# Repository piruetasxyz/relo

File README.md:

# relo
módulo de señal de reloj

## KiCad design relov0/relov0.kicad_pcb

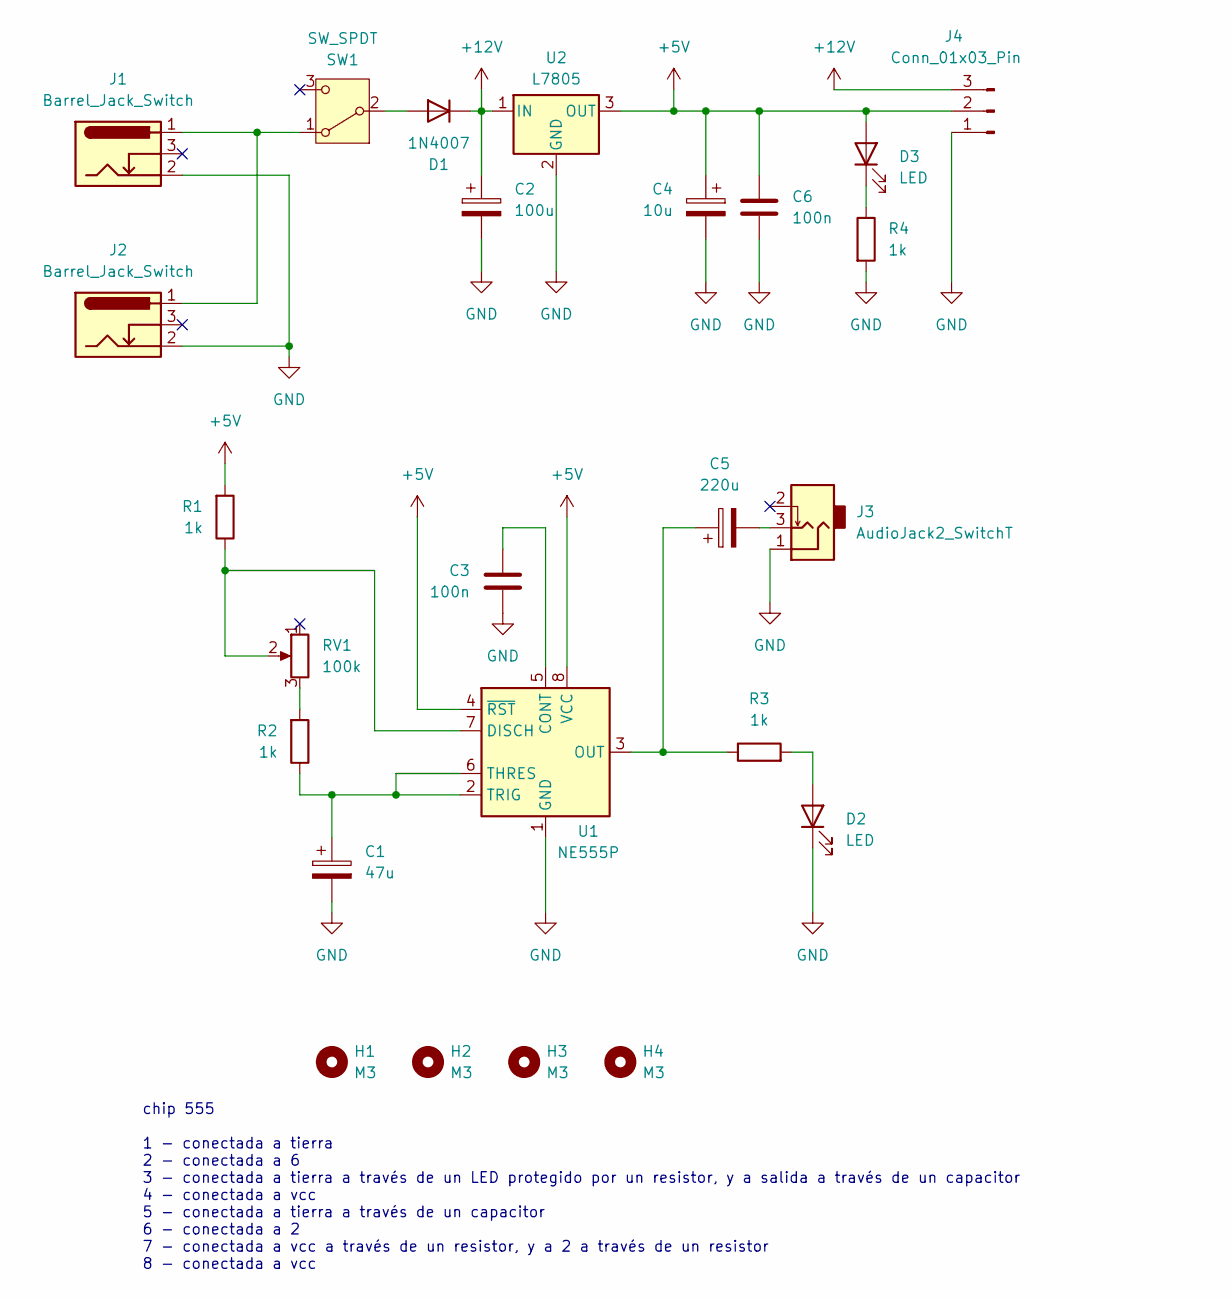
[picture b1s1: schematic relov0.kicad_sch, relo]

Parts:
C1: 47u; CP_Radial_D5.0mm_P2.00mm
C2: 100u; CP_Radial_D8.0mm_P3.80mm
C3, C6: 100n; C_Disc_D5.0mm_W2.5mm_P2.50mm
C4: 10u; CP_Radial_D4.0mm_P2.00mm
C5: 220u; CP_Radial_D5.0mm_P2.00mm
D1: 1N4007; D_DO-41_SOD81_P10.16mm_Horizontal
D2, D3: LED; LED_D5.0mm
H1, H2, H3, H4: M3; MountingHole_3.2mm_M3
J1, J2: Barrel_Jack_Switch; BarrelJack_Horizontal
J3: AudioJack2_SwitchT; PJ301M-12
J4: Conn_01x03_Pin; PinSocket_1x03_P2.54mm_Vertical
R1, R2, R3, R4: 1k; R_Axial_DIN0207_L6.3mm_D2.5mm_P10.16mm_Horizontal
RV1: 100k; Potentiometer_Alps_RK163_Single_Horizontal
SW1: SW_SPDT; spdt_ssd12d00g3
U1: NE555P; DIP-8_W7.62mm_Socket_LongPads
U2: L7805; TO-220-3_Horizontal_TabDown

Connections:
+5V: C4.1, C6.1, D3.2 (A), J4.2, R1.2, U1.4 (~RST), U1.8 (VCC), U2.3 (OUT)
+12V: C2.1, D1.1 (K), J4.3, U2.1 (IN)
GND: C1.2, C2.2, C3.1, C4.2, C6.2, D2.1 (K), J1.2, J2.2, J3.1, J4.1, R4.2, U1.1 (GND), U2.2 (GND)
unnamed: C5.2, J3.3
unnamed: D1.2 (A), SW1.2 (B)
unnamed: D2.2 (A), R3.2
unnamed: D3.1 (K), R4.1
unnamed: R2.2, RV1.3
unnamed: J1.1, J2.1, SW1.1 (A)
unnamed: C3.2, U1.5 (CONT)
unnamed: R1.1, RV1.2, U1.7 (DISCH)
unnamed: C5.1, R3.1, U1.3 (OUT)
unnamed: C1.1, R2.1, U1.2 (TRIG), U1.6 (THRES)

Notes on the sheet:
chip 555 1 - conectada a tierra 2 - conectada a 6 3 - conectada a tierra a través de un LED protegido por un resistor, y a salida a través de un capacitor 4 - conectada a vcc 5 - conectada a tierra a través de un capacitor 6 - conectada a 2 7 - conectada a vcc a través de un resistor, y a 2 a travé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

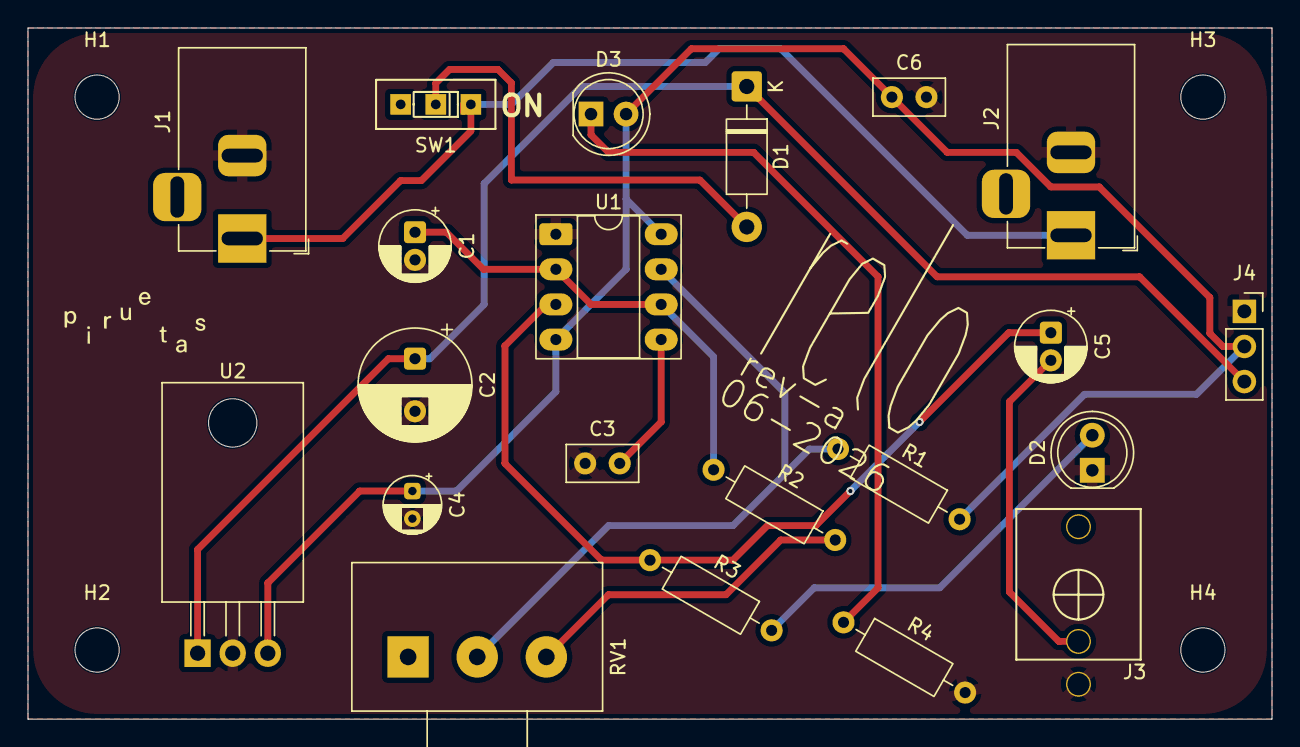
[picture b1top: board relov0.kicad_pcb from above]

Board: 2 copper layers, 90.0 x 50.0 mm, 25 parts (0 on the bottom side), 13 nets.

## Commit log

2026-06-01 agregar .gitignore
2026-06-01 agregar proyecto vacio
2026-06-01 agregar archivos de kicad a gitignore
2026-06-01 agregar nueva version del proyecto
2026-06-02 agregar biblioteca relo y actualizar footprints
2026-06-02 agregar pcb
2026-06-02 agregar nuevas mods
2026-06-06 agregar graficas
2026-06-06 agregar vias
2026-06-06 añadido gerb
2026-06-06 agregar en .zip
